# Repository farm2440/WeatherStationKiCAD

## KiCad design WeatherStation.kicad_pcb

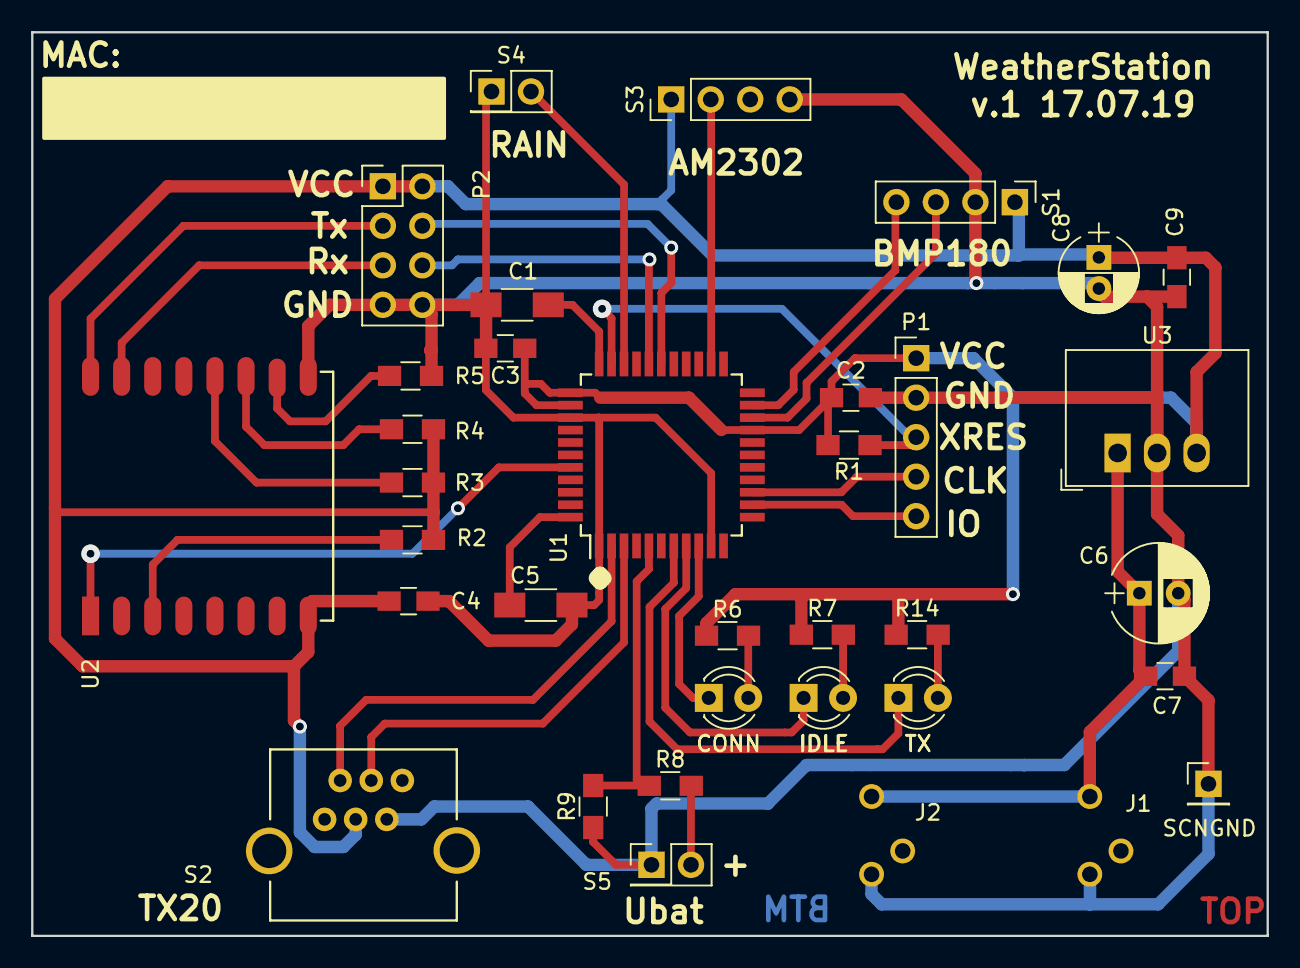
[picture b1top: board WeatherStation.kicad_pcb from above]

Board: 2 copper layers, 79.4 x 58.1 mm, 35 parts (0 on the bottom side), 31 nets.

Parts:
C1, C5: 1u; C_1206_HandSoldering
C2, C3, C4: 100n; C_0805_HandSoldering
C6: 100uF; CP_Radial_D6.3mm_P2.50mm
C7, C9: 100nF; C_0805_HandSoldering
C8: 47uF; CP_Radial_D5.0mm_P2.00mm
CONN: CONN; LED_D3.0mm
IDLE: IDLE; LED_D3.0mm
J1, J2: Conn_01x03; DC_JACK_3mm_A
P1: PROG; Pin_Header_Straight_1x05_Pitch2.54mm
P2: CONN_02X04; Pin_Header_Straight_2x04_Pitch2.54mm
R1, R8, R9: 4k7; R_0805_HandSoldering
R2, R3, R4, R5: 2k7; R_0805_HandSoldering
R6, R7, R14: 1k; R_0805_HandSoldering
S1: BMP180; Socket_Strip_Straight_1x04_Pitch2.54mm
S2: TX20; RJ12_E
S3: AM2302; Socket_Strip_Straight_1x04_Pitch2.54mm
S4: RAIN; Pin_Header_Straight_2x01_Pitch2.54mm
S5: UBAT; Pin_Header_Straight_2x01_Pitch2.54mm
SCNGND: SCNGND; Pin_Header_Straight_1x01_Pitch2.54mm
TX: TX; LED_D3.0mm
U1: CY8C4245AXI-483; LQFP-44_10x10mm_Pitch0.8mm
U2: ESP-07v2; ESP-07v2s
U3: AMSR-783.3-NZ; DCDC-Conv_Recom_R-78HBxx-0.5

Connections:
+3V3: C2.1, C3.1, C4.1, C8.1, C9.1, P1.1, P2.1, P2.2, R1.2, R2.1, R3.2, R4.2, R6.1, R7.1, R14.1, S1.1, S2.3, S3.1, U1.19, U1.34, U1.35, U2.8, U3.3
DBG-CLK: P1.4, U1.14
DBG-IO: P1.5, U1.13
GND: C1.2, C2.2, C3.2, C4.2, C5.2, C6.2, C7.2, C8.2, C9.2, J1.2, J2.2, P1.2, P2.7, P2.8, R5.2, R9.1, S1.2, S2.5, S3.4, S4.1, S5.1, SCNGND.1, U1.1, U1.10, U1.36, U2.9, U3.2
GREEN: IDLE.1, U1.8
HUM: S3.2, U1.24
unnamed: C1.1, U1.33
unnamed: C5.1, U1.44
unnamed: C6.1, C7.1, J1.1, J2.1, U3.1
unnamed: CONN.2, R6.2
unnamed: IDLE.2, R7.2
unnamed: R14.2, TX.2
unnamed: P2.3, U2.16
unnamed: P2.5, U2.15
unnamed: R2.2, U2.3
unnamed: R3.1, U2.12
unnamed: R4.1, U2.11
unnamed: R5.1, U2.10
unnamed: R8.2, S5.2
unnamed: U2.1, U2.4
RAIN: S4.2, U1.31
RED: CONN.1, U1.9
RX: P2.6, U1.29
SCL: S1.3, U1.20
SDA: S1.4, U1.21
TX: P2.4, U1.28
UBAT: R8.1, R9.2, U1.5
WindCE: S2.4, U1.3
WindRX: S2.2, U1.2
XRES: P1.3, R1.1, U1.32
YELLOW: TX.1, U1.7

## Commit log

2020-01-10 Schematic and PCB v.1 purchaced from AllPCB
